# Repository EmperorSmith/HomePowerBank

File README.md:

# HomePowerBank

This project is a combined hardware-software effort around designing a control / management system for a home power bank. Unlike commercial USB power banks, this one is intended to serve as a sort of "generator substitute," having a stack of batteries large enough to supply an inverter during situations that otherwise lack power (general outage, off-grid living, etc).

# Design Goals

## Primary Goals

- Monitor a multi-cell battery stack
    - Measure cell voltage
    - Measure stack voltage
    - Measure stack current
    - Measure temperatures
    - Estimate cell state-of-charge
- Report monitored state to user
- Accept and react to user input for basic operations
- Protect pack against fault conditions
    - Overvoltage / Overcharge
    - Undervoltage / Undercharge
    - Overcurrent
    - Overtemperature
- Integrate control of external charger and inverter
    - Connect & disconnect battery stack bus and external devices
    - Produce on/off control output to charger
    - Take in fault input from charger
    - Produce on/off control output to inverter
    - Take in fault input from inverter

## Secondary Goals

- Provide bidirectional USB-C charging port
    - Supply external loads with 5V 1.5A power
    - Trickle-charge bank from external supply
- Take control commands from external communication interface
- Implement advanced diagnostics
- Implement flexible / extensible stack architecture
    - Adapt to different cell and IC counts
    - Adapt to different cell chemistries

# Tools

As much as possible, the tools used to produce the design should be freely available.

- Circuit schematic and layout creation will take place in [KiCAD](www.kicad.org)
- Block diagrams and similar drawing should use [draw.io](www.diagrams.net)
- Circuit simulations should be conducted in a free SPICE tool, like [ngspice](https://ngspice.sourceforge.io/) or [LTSpice](https://www.analog.com/en/resources/design-tools-and-calculators/ltspice-simulator.html)
- Documentation should be created using the Markdown language / format

# Philosophy

## System Design

When in doubt, design should err on the side of over-engineering, especially for the prototype phase.

## Project Code of Conduct

"Be excellent to each other" *- Bill S. Preston, Esq.*

## Usability

The system in basic form should be fully usable from the standpoint of a non-engineer, but should also offer the capabilities for a knowledgeable person to modify / alter the system to their desires.

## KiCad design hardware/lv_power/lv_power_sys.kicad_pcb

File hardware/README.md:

# System Blocks

## Internal Power Supply

### Description

This system will take the battery bank voltage and convert it to 5V to supply various aspects of the system (microcontroller, USB port, maybe even the BMS chips).

With the battery bank currently targeted at a 16S LFP configuration, this limits the maximum voltage to about 55V. Conventional buck regulators should be able to convert at this ratio and voltage range. It is also permissible to use a flyback regulator, although this will present additional challenges over a buck regulator.

If other system rails are needed, secondary voltage regulators will be added.

There will be a secondary LV battery backup system to ensure that faults with the main bank will not cause immediate shutdown of the system. This is to ensure good shutdown and startup behavior and preserve information about the system.

### Requirements

- Input Voltage : 32V to 56V
- Input Current : (as needed)
- Output Voltage : 5V +/- 0.2V
- Output Current : at least 1.5A, no more than 3A

## Trickle Charge Circuit

### Description

This system will take in 5V from the USB port and boost it up to about 55V to trickle-charge the battery bank.

The power conversion topology chosen is a flyback converter. The step-up ratio is just too large to use a conventional boost converter.

Ideally, the output of the buck regulator will have a constant-current-limiting circuit attached to it to accommodate a wide range of battery bank voltages.

### Requirements

- Input Voltage : 5.0V +/- 0.25V
- Input Current : no more than 1A average
- Output Voltage : 53V +/- 2V
- Output Current : no more than 50mA

## USB Interface

### Description

A USB C socket will be present on the unit. It will be capable of both supplying power to an external load and drawing power from an external source.

### Requirements

Despite having a USB C connector, the port will not have full USB 3 communication capabilities. If communication is added, it will be USB 2.x compliant only.

While the port will be able to both source and sink power, USB PD communication will not be implemented. Instead, a user-activated switch will determine the direction of the power flow. On switch toggle, the USB port will fully disconnect, then reconfigure the CC pins as necessary and monitor for connection.

When sourcing power, the interface will use CC pin resistor strapping to communicate the availability of up to 1.5A of current at 5.0V to downstream devices.

When sinking power, the interface will measure the CC pin voltage and respect the current limits communicated in that manner. The trickle charge circuit will not activate unless at least 1.5A of current is available from the upstream device.

The USB port will include a power switch and current sense amplifier to monitor operation. Fault conditions will trigger a port shutdown. Reconnection will be attempted after a timeout.

## Microcontroller

### Description

A local microcontroller will handle all operation and monitoring of the battery bank and attached systems (charger, inverter, USB-attached device). It will interface with users only in the most basic of manners (buttons / switches / LED indicators). More complex interactions will require an external device, to which the microcontroller will provide information for futher processing and display. The microcontroller will retain key state information across power cycles.

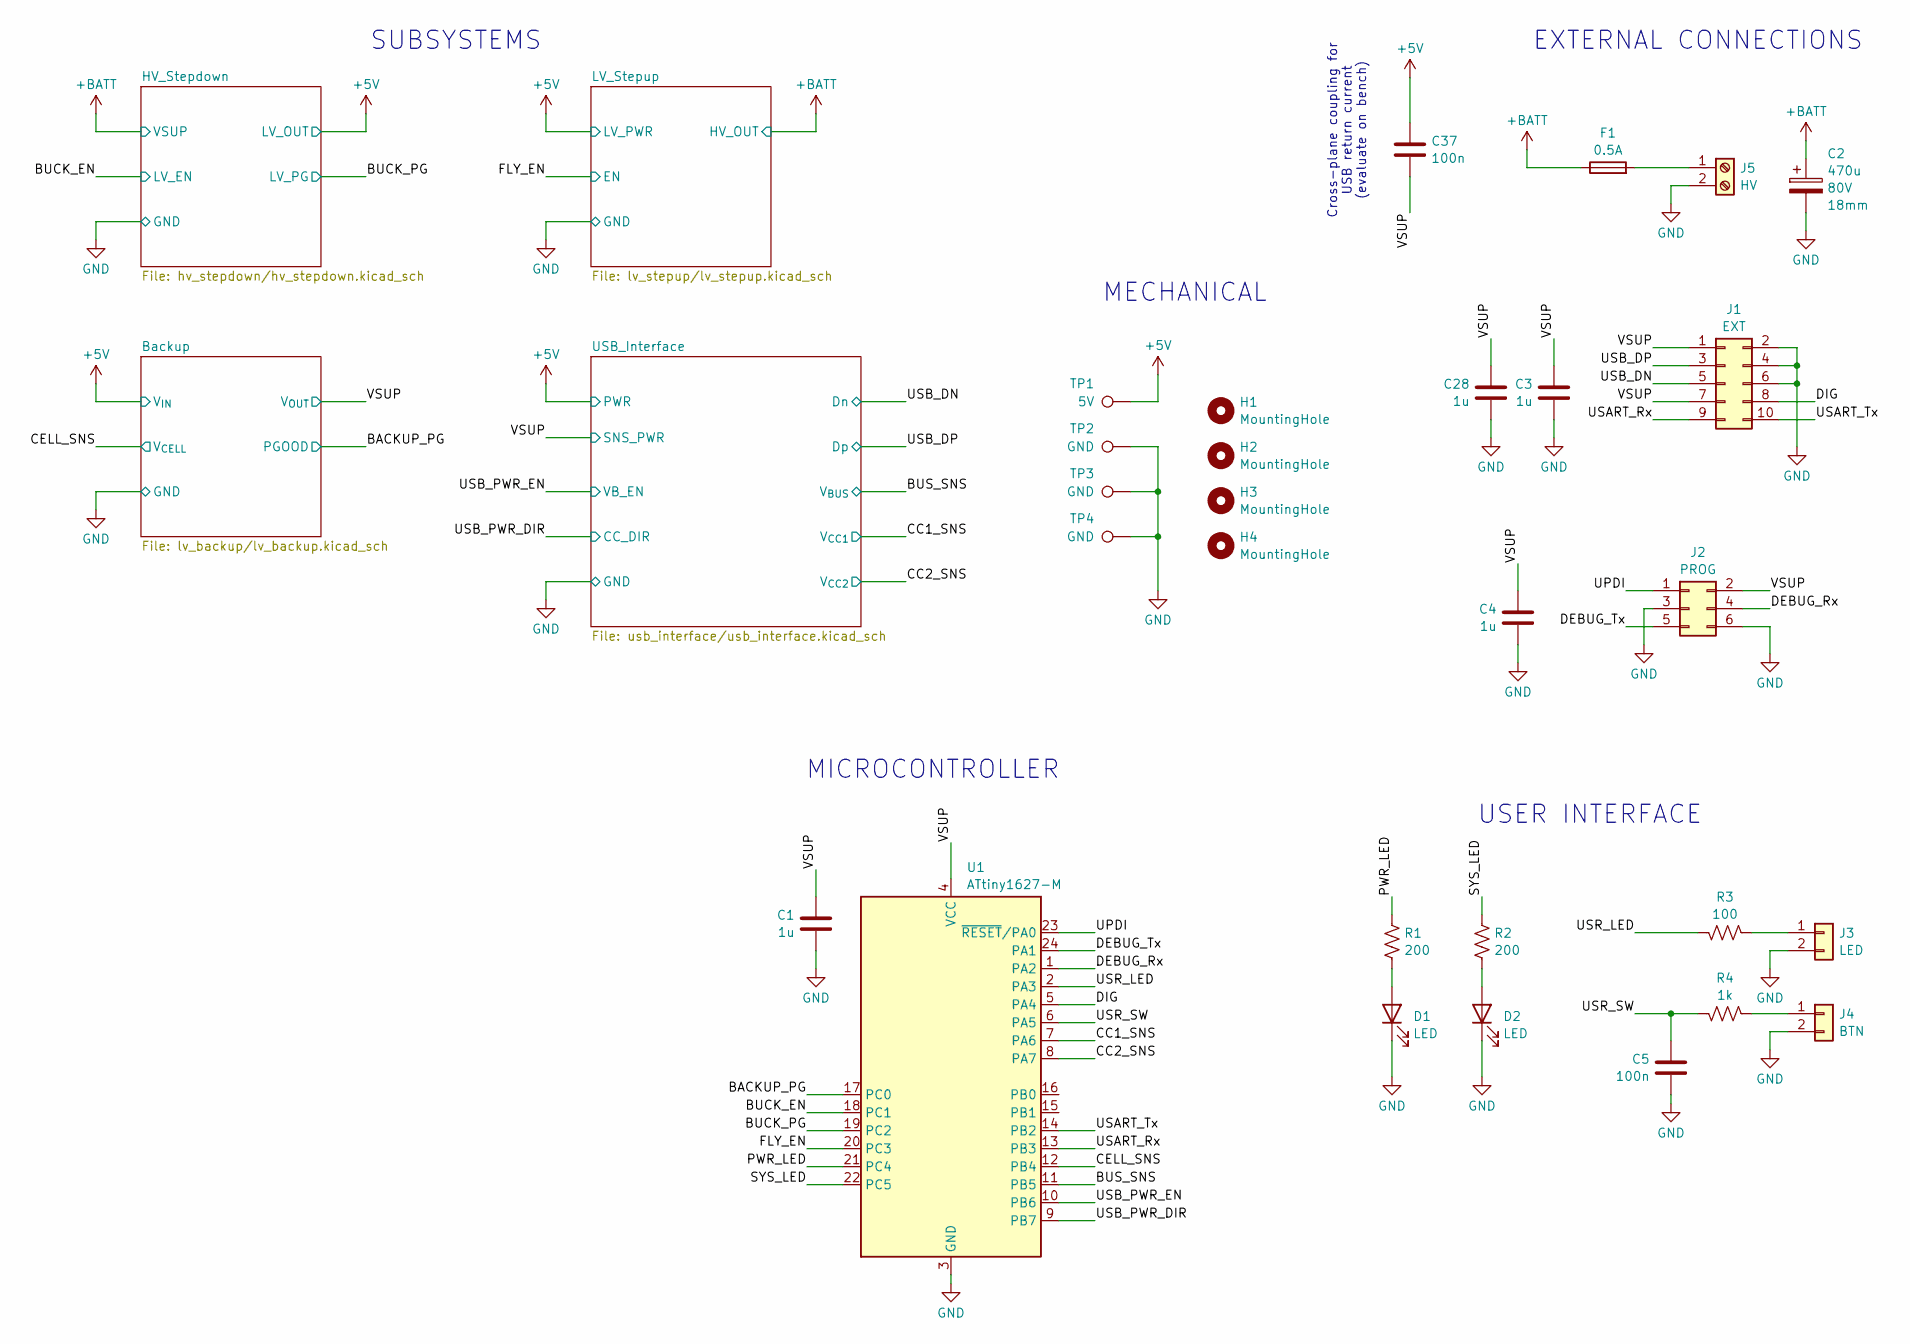
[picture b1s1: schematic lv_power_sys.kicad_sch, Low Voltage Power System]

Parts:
C1, C3, C4, C28: 1u; C_0603_1608Metric
C2: 470u; CP_Elec_18x17.5
C5, C37: 100n; C_0603_1608Metric
D1, D2: LED; D_0603_1608Metric
F1: 0.5A; Fuseholder_Clip-5x20mm_Keystone_3512_Inline_P23.62x7.27mm_D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
H1, H2, H3, H4: MountingHole; MountingHole_3.2mm_M3
J1: EXT; IDC-Header_2x05_P2.54mm_Vertical
J2: PROG; PinHeader_2x03_P2.54mm_Vertical
J3: LED; PinHeader_1x02_P2.54mm_Vertical
J4: BTN; PinHeader_1x02_P2.54mm_Vertical
J5: HV; SolderWire-0.15sqmm_1x02_P4mm_D0.5mm_OD1.5mm
R1, R2: 200; R_0603_1608Metric
R3: 100; R_0603_1608Metric
R4: 1k; R_0603_1608Metric
TP1: 5V; TestPoint_Pad_D1.5mm
TP2, TP3, TP4: GND; TestPoint_Pad_D1.5mm
U1: ATtiny1627-M; QFN-24-1EP_4x4mm_P0.5mm_EP2.6x2.6mm

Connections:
+5V: C37.1, TP1.1; also elsewhere on the board
+BATT: C2.1, F1.1; also elsewhere on the board
/BACKUP_PG: U1.17 (PC0); also elsewhere on the board
/BUCK_EN: U1.18 (PC1); also elsewhere on the board
/BUCK_PG: U1.19 (PC2); also elsewhere on the board
/BUS_SNS: U1.11 (PB5); also elsewhere on the board
/CC1_SNS: U1.7 (PA6); also elsewhere on the board
/CC2_SNS: U1.8 (PA7); also elsewhere on the board
/CELL_SNS: U1.12 (PB4); also elsewhere on the board
/DEBUG_Rx: J2.4, U1.1 (PA2)
/DEBUG_Tx: J2.5, U1.24 (PA1)
/DIG: J1.8, U1.5 (PA4)
/FLY_EN: U1.20 (PC3); also elsewhere on the board
/LED0: R1.2, U1.21 (PC4)
/LED1: R2.2, U1.22 (PC5)
/UPDI: J2.1, U1.23 (~RESET/PA0)
/USART_Rx: J1.9, U1.13 (PB3)
/USART_Tx: J1.10, U1.14 (PB2)
/USB_DN: J1.5; also elsewhere on the board
/USB_DP: J1.3; also elsewhere on the board
/USB_PWR_DIR: U1.9 (PB7); also elsewhere on the board
/USB_PWR_EN: U1.10 (PB6); also elsewhere on the board
/USR_LED: R3.1, U1.2 (PA3)
/USR_SW: C5.1, R4.1, U1.6 (PA5)
/VSUP: C1.1, C3.1, C4.1, C28.1, C37.2, J1.1, J1.7, J2.2, U1.4 (VCC); also elsewhere on the board
GND: C1.2, C2.2, C3.2, C4.2, C5.2, C28.2, D1.1 (K), D2.1 (K), J1.2, J1.4, J1.6, J2.3, J2.6, J3.2, J4.2, J5.2, TP2.1, TP3.1, TP4.1, U1.3 (GND), U1.25 (GND); also elsewhere on the board
unnamed: D1.2 (A), R1.1
unnamed: D2.2 (A), R2.1
unnamed: J3.1, R3.2
unnamed: J4.1, R4.2
unnamed: F1.2, J5.1

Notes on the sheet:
USER INTERFACE
SUBSYSTEMS
EXTERNAL CONNECTIONS
Cross-plane coupling for USB return current (evaluate on bench)
MECHANICAL
MICROCONTROLLER

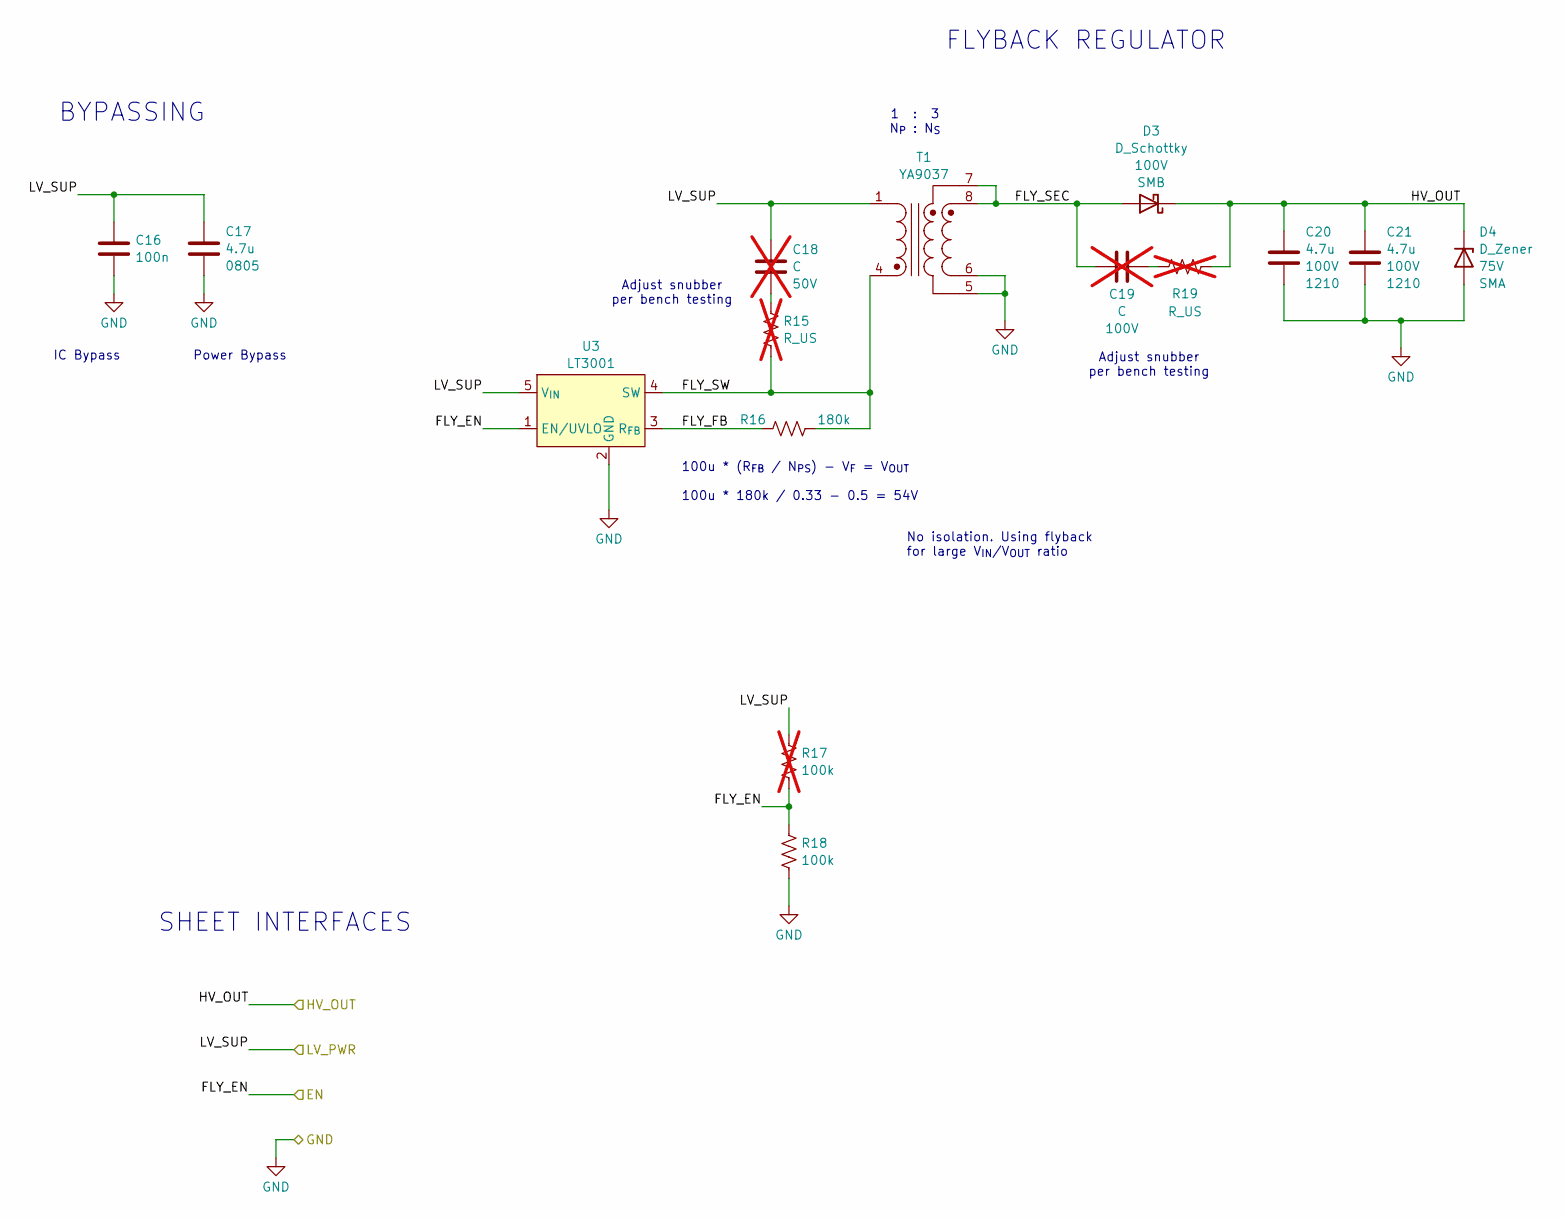
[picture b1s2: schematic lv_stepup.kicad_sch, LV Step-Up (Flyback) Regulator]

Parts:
C16: 100n; C_0603_1608Metric
C17: 4.7u; C_0805_2012Metric
C18, C19: C; C_0603_1608Metric; not fitted
C20, C21: 4.7u; C_1210_3225Metric
D3: D_Schottky; D_SMB
D4: D_Zener; D_SMA
R15, R19: R_US; R_0603_1608Metric; not fitted
R16: 180k; R_0603_1608Metric
R17: 100k; R_0603_1608Metric; not fitted
R18: 100k; R_0603_1608Metric
T1: YA9037; Coilcraft_YA903x
U3: LT3001; SOT-23-5

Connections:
+5V: C16.1, C17.1, C18.1, R17.2, T1.1, U3.5 (V_{IN}); also elsewhere on the board
+BATT: C20.1, C21.1, D3.1 (K), D4.1 (K), R19.2; also elsewhere on the board
/FLY_EN: R17.1, R18.2, U3.1 (EN/UVLO); also elsewhere on the board
/LV_Stepup/FLY_FB: R16.1, U3.3 (R_{FB})
/LV_Stepup/FLY_SEC: C19.1, D3.2 (A), T1.7, T1.8
/LV_Stepup/FLY_SW: R15.1, R16.2, T1.4, U3.4 (SW)
GND: C16.2, C17.2, C20.2, C21.2, D4.2 (A), R18.1, T1.5, T1.6, U3.2 (GND); also elsewhere on the board
unnamed: C18.2, R15.2
unnamed: C19.2, R19.1

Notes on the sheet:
No isolation. Using flyback for large V_{IN}/V_{OUT} ratio
IC Bypass
1 : 3 N_{P} : N_{S}
FLYBACK REGULATOR
100u * (R_{FB} / N_{PS}) - V_{F} = V_{OUT} 100u * 180k / 0.33 - 0.5 = 54V
SHEET INTERFACES
Adjust snubber per bench testing
Power Bypass
BYPASSING

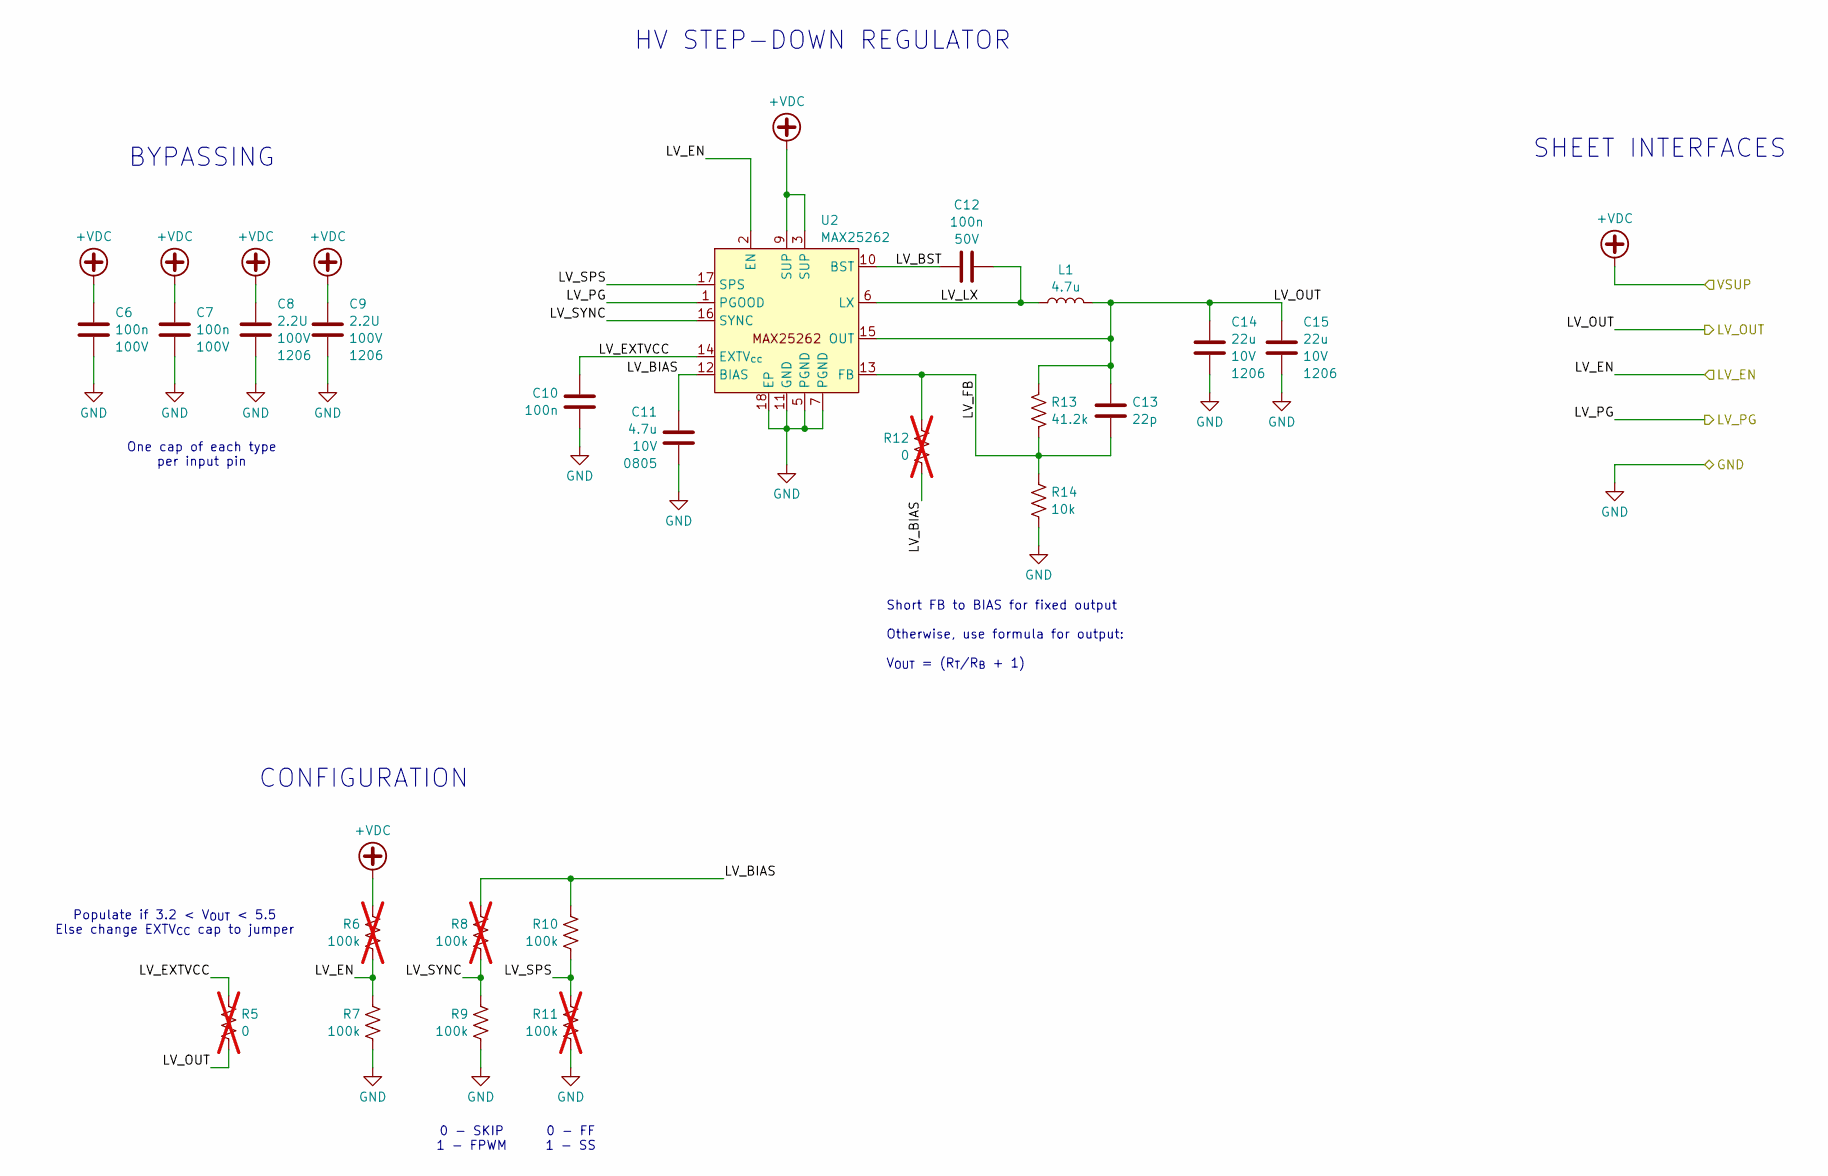
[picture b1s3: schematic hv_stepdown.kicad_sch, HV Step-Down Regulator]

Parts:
C6, C7, C10, C12: 100n; C_0603_1608Metric
C8, C9: 2.2U; C_1210_3225Metric
C11: 4.7u; C_0805_2012Metric
C13: 22p; C_0603_1608Metric
C14, C15: 22u; C_1210_3225Metric
L1: 4.7u; L_Coilcraft_XAL6060-XXX
R5, R12: 0; R_0603_1608Metric; not fitted
R6, R8, R11: 100k; R_0603_1608Metric; not fitted
R7, R9, R10: 100k; R_0603_1608Metric
R13: 41.2k; R_0603_1608Metric
R14: 10k; R_0603_1608Metric
U2: MAX25262; ADI_21-100429

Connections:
+5V: C13.2, C14.2, C15.2, L1.2, R5.1, R13.2, U2.15 (OUT); also elsewhere on the board
+BATT: C6.1, C7.1, C8.1, C9.1, R6.1, U2.3 (SUP), U2.9 (SUP); also elsewhere on the board
/BUCK_EN: R6.2, R7.1, U2.2 (EN); also elsewhere on the board
/BUCK_PG: U2.1 (PGOOD); also elsewhere on the board
/HV_Stepdown/LV_BIAS: C11.2, R8.1, R10.1, R12.2, U2.12 (BIAS)
/HV_Stepdown/LV_BST: C12.1, U2.10 (BST)
/HV_Stepdown/LV_EXTVCC: C10.1, R5.2, U2.14 (EXTV_{cc})
/HV_Stepdown/LV_FB: C13.1, R12.1, R13.1, R14.2, U2.13 (FB)
/HV_Stepdown/LV_LX: C12.2, L1.1, U2.6 (LX)
/HV_Stepdown/LV_SPS: R10.2, R11.1, U2.17 (SPS)
/HV_Stepdown/LV_SYNC: R8.2, R9.1, U2.16 (SYNC)
GND: C6.2, C7.2, C8.2, C9.2, C10.2, C11.1, C14.1, C15.1, R7.2, R9.2, R11.2, R14.1, U2.5 (PGND), U2.7 (PGND), U2.11 (GND), U2.18 (EP); also elsewhere on the board

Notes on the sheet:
HV STEP-DOWN REGULATOR
0 - SKIP 1 - FPWM
Populate if 3.2 < V_{OUT} < 5.5 Else change EXTV_{CC} cap to jumper
0 - FF 1 - SS
SHEET INTERFACES
Short FB to BIAS for fixed output Otherwise, use formula for output: V_{OUT} = (R_{T}/R_{B} + 1)
CONFIGURATION
BYPASSING
One cap of each type per input pin

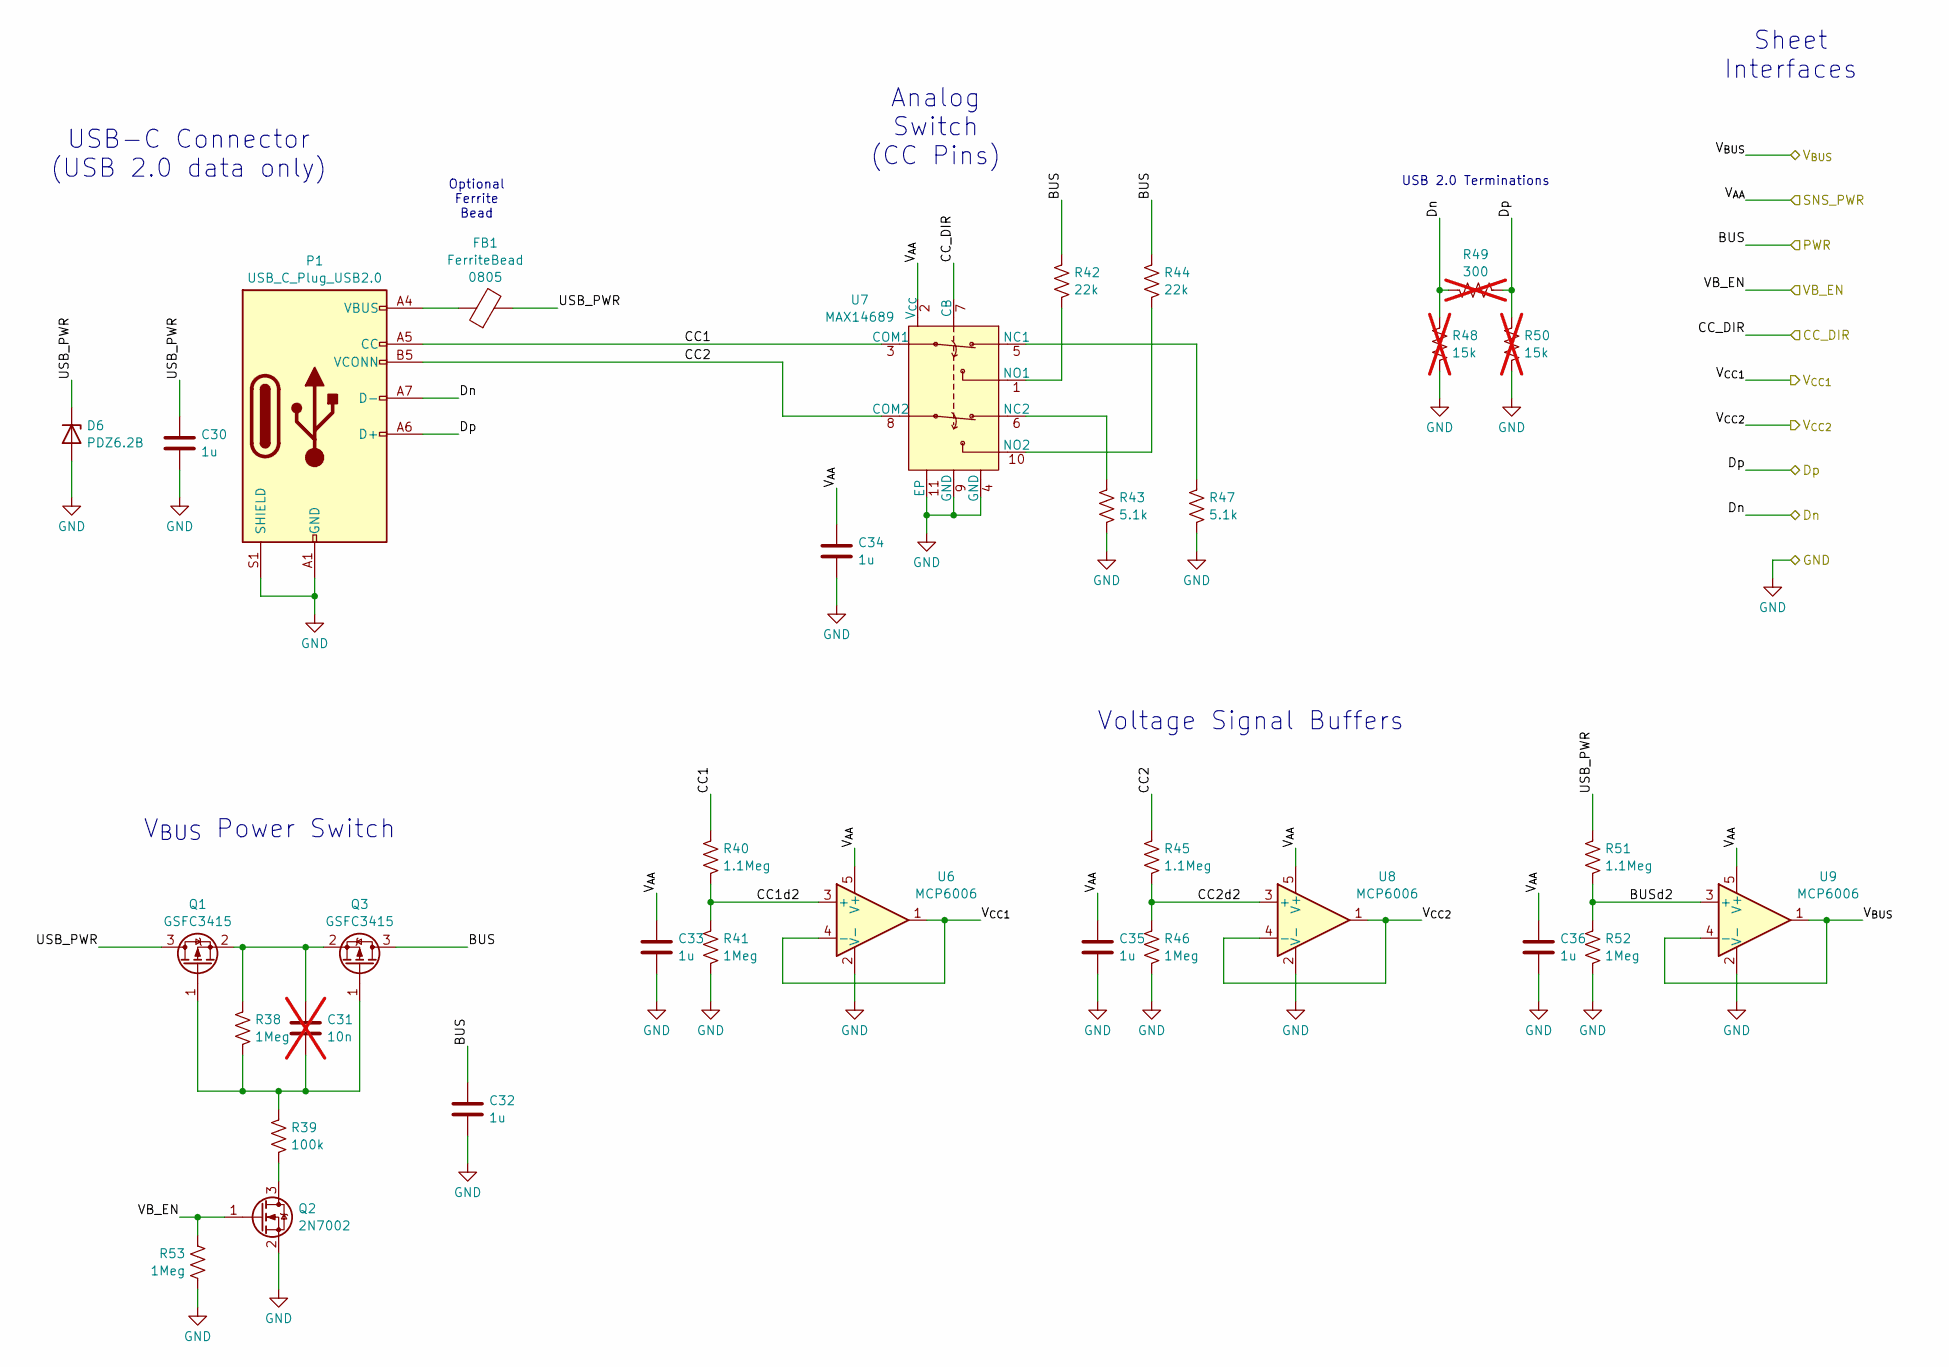
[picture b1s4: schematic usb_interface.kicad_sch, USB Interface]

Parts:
C30, C32, C33, C34, C35, C36: 1u; C_0603_1608Metric_Pad1.08x0.95mm_HandSolder
C31: 10n; C_0603_1608Metric; not fitted
D6: PDZ6.2B; D_SOD-123
FB1: FerriteBead; L_0805_2012Metric
P1: USB_C_Plug_USB2.0; USB_C_Receptacle_GCT_USB4085
Q1, Q3: GSFC3415; SOT-23
Q2: 2N7002; SOT-23
R38, R41, R46, R52, R53: 1Meg; R_0603_1608Metric
R39: 100k; R_0603_1608Metric
R40, R45, R51: 1.1Meg; R_0603_1608Metric
R42, R44: 22k; R_0603_1608Metric
R43, R47: 5.1k; R_0603_1608Metric
R48, R50: 15k; R_0603_1608Metric; not fitted
R49: 300; R_0603_1608Metric; not fitted
U6, U8, U9: MCP6006; TSOT-23-5
U7: MAX14689; ADI_21-100013A

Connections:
+5V: C32.1, Q3.3 (D), R42.1, R44.1; also elsewhere on the board
/BUS_SNS: U9.1, U9.4 (-); also elsewhere on the board
/CC1_SNS: U6.1, U6.4 (-); also elsewhere on the board
/CC2_SNS: U8.1, U8.4 (-); also elsewhere on the board
/USB_DN: P1.A7 (D-), R48.1, R49.1; also elsewhere on the board
/USB_DP: P1.A6 (D+), R49.2, R50.1; also elsewhere on the board
/USB_Interface/BUSd2: R51.2, R52.1, U9.3 (+)
/USB_Interface/CC1: P1.A5 (CC), R40.1, U7.3 (COM1)
/USB_Interface/CC1d2: R40.2, R41.1, U6.3 (+)
/USB_Interface/CC2: P1.B5 (VCONN), R45.1, U7.8 (COM2)
/USB_Interface/CC2d2: R45.2, R46.1, U8.3 (+)
/USB_Interface/USB_PWR: C30.1, D6.1 (K), FB1.2, Q1.3 (D), R51.1
/USB_PWR_DIR: U7.7 (CB); also elsewhere on the board
/USB_PWR_EN: Q2.1 (G), R53.1; also elsewhere on the board
/VSUP: C33.1, C34.1, C35.1, C36.1, U6.5 (V+), U7.2 (V_{CC}), U8.5 (V+), U9.5 (V+); also elsewhere on the board
GND: C30.2, C32.2, C33.2, C34.2, C35.2, C36.2, D6.2 (A), P1.A1 (GND), P1.A12 (GND), P1.B1 (GND), P1.B12 (GND), P1.S1 (SHIELD), Q2.2 (S), R41.2, R43.2, R46.2, R47.2, R48.2, R50.2, R52.2, R53.2, U6.2 (V-), U7.4 (GND), U7.9 (GND), U7.11 (EP), U8.2 (V-), U9.2 (V-); also elsewhere on the board
unnamed: FB1.1, P1.A4 (VBUS), P1.A9 (VBUS), P1.B4 (VBUS), P1.B9 (VBUS)
unnamed: C31.2, Q1.1 (G), Q3.1 (G), R38.2, R39.1
unnamed: C31.1, Q1.2 (S), Q3.2 (S), R38.1
unnamed: Q2.3 (D), R39.2
unnamed: R47.1, U7.5 (NC1)
unnamed: R43.1, U7.6 (NC2)
unnamed: R42.2, U7.1 (NO1)
unnamed: R44.2, U7.10 (NO2)

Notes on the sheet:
Sheet Interfaces
V_{BUS} Power Switch
Analog Switch (CC Pins)
Optional Ferrite Bead
Voltage Signal Buffers
USB-C Connector (USB 2.0 data only)
USB 2.0 Terminations

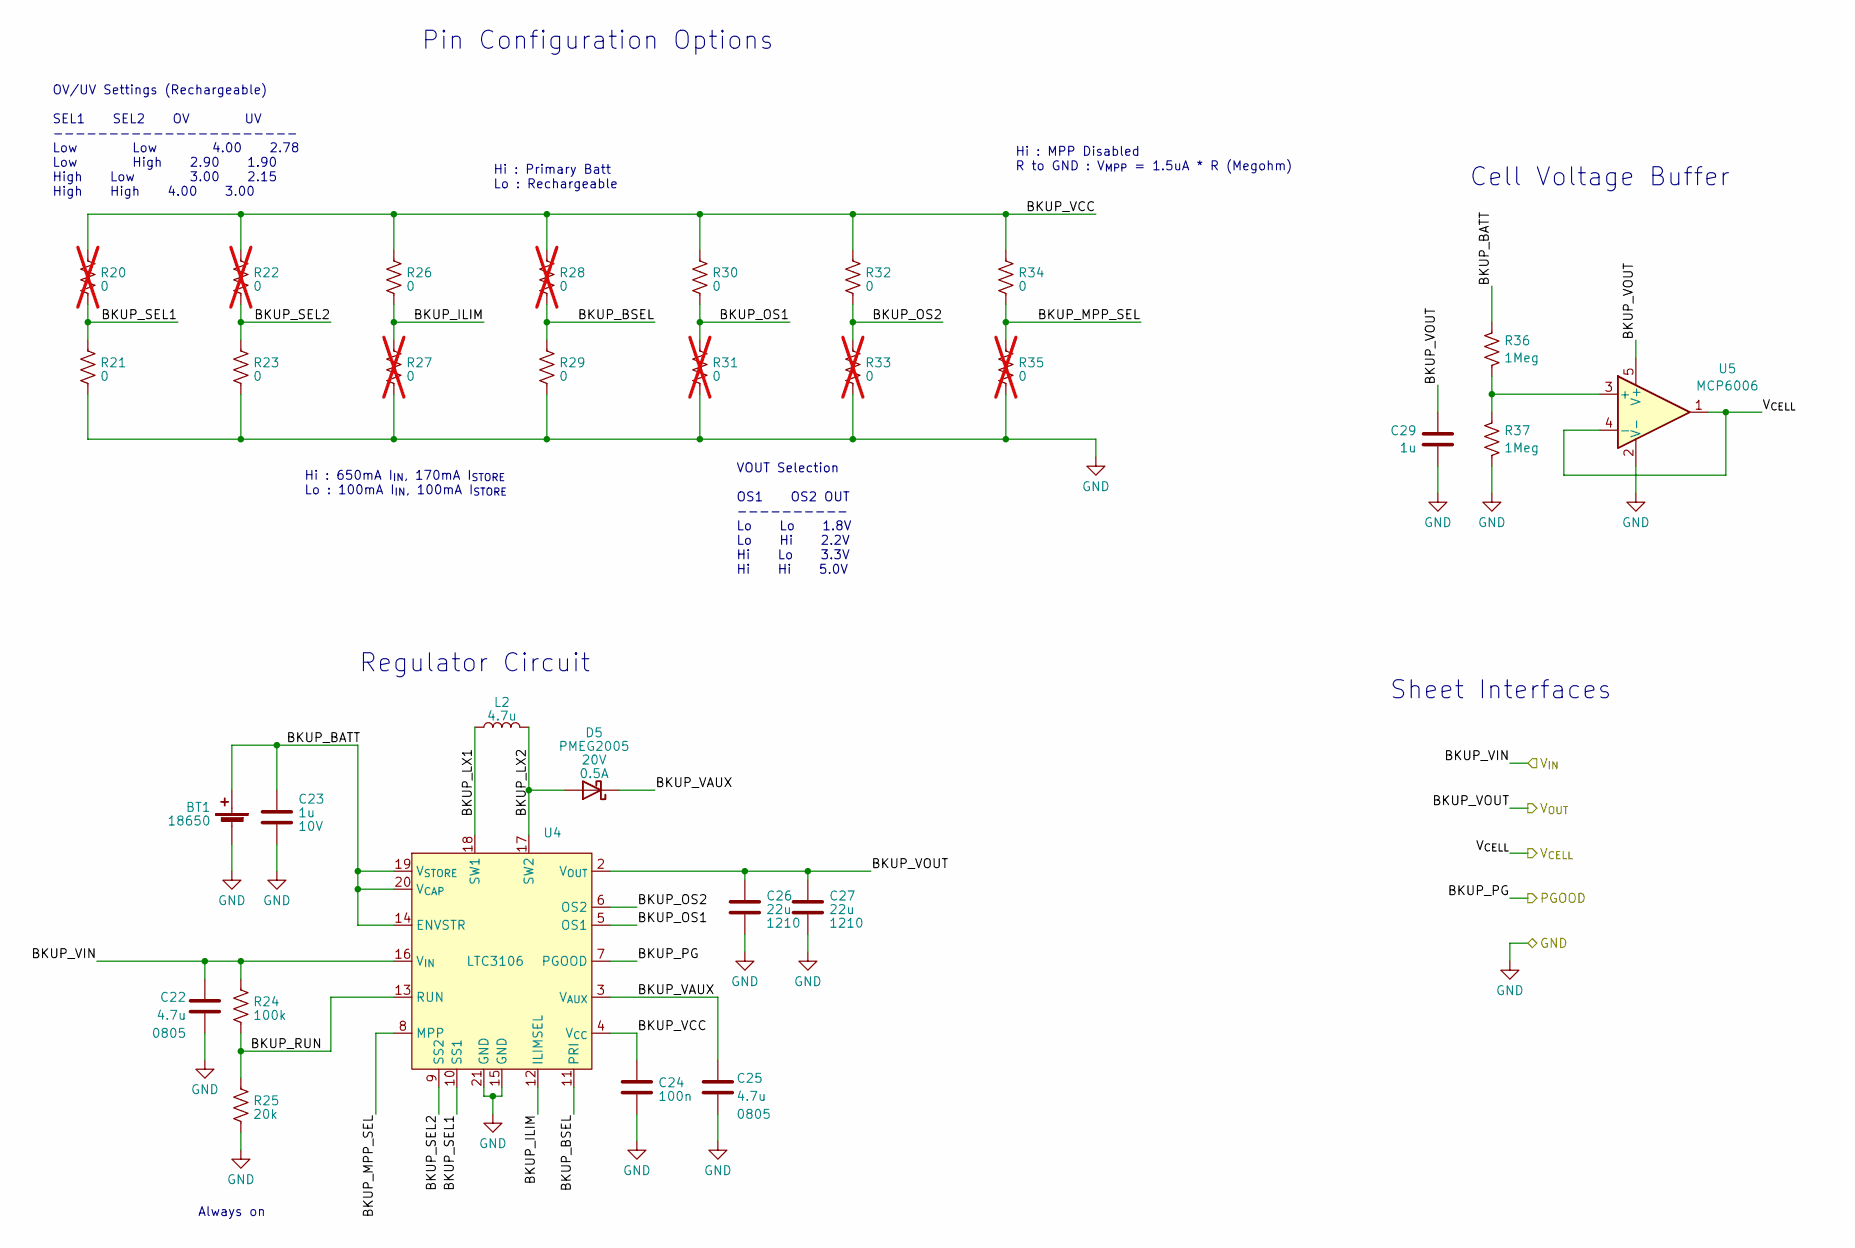
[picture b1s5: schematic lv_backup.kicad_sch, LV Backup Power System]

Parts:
BT1: 18650; BatteryHolder_Keystone_1042_1x18650
C22, C25: 4.7u; C_0805_2012Metric
C23: 1u; C_0603_1608Metric_Pad1.08x0.95mm_HandSolder
C24: 100n; C_0603_1608Metric
C26, C27: 22u; C_1210_3225Metric
C29: 1u; C_0603_1608Metric
D5: PMEG2005; D_SOD-123F
L2: 4.7u; L_Coilcraft_XAL4040-XXX
R20, R22, R27, R28, R31, R33, R35: 0; R_0603_1608Metric; not fitted
R21, R23, R26, R29, R30, R32, R34: 0; R_0603_1608Metric
R24: 100k; R_0603_1608Metric
R25: 20k; R_0603_1608Metric
R36, R37: 1Meg; R_0603_1608Metric
U4: LTC3106; QFN-20-1EP_3x4mm_P0.5mm_EP1.65x2.65mm
U5: MCP6006; TSOT-23-5

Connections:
+5V: C22.1, R24.1, U4.16 (V_{IN}); also elsewhere on the board
/BACKUP_PG: U4.7 (PGOOD); also elsewhere on the board
/Backup/BKUP_BATT: BT1.1 (+), C23.1, R36.1, U4.14 (ENVSTR), U4.19 (V_{STORE}), U4.20 (V_{CAP})
/Backup/BKUP_BSEL: R28.2, R29.1, U4.11 (PRI)
/Backup/BKUP_ILIM: R26.2, R27.1, U4.12 (ILIMSEL)
/Backup/BKUP_LX1: L2.1, U4.18 (SW1)
/Backup/BKUP_LX2: D5.2 (A), L2.2, U4.17 (SW2)
/Backup/BKUP_MPP_SEL: R34.2, R35.1, U4.8 (MPP)
/Backup/BKUP_OS1: R30.2, R31.1, U4.5 (OS1)
/Backup/BKUP_OS2: R32.2, R33.1, U4.6 (OS2)
/Backup/BKUP_RUN: R24.2, R25.1, U4.13 (RUN)
/Backup/BKUP_SEL1: R20.2, R21.1, U4.10 (SS1)
/Backup/BKUP_SEL2: R22.2, R23.1, U4.9 (SS2)
/Backup/BKUP_VAUX: C25.1, D5.1 (K), U4.3 (V_{AUX})
/Backup/BKUP_VCC: C24.1, R20.1, R22.1, R26.1, R28.1, R30.1, R32.1, R34.1, U4.4 (V_{CC})
/CELL_SNS: U5.1, U5.4 (-); also elsewhere on the board
/VSUP: C26.1, C27.1, C29.1, U4.2 (V_{OUT}), U5.5 (V+); also elsewhere on the board
GND: BT1.2 (-), C22.2, C23.2, C24.2, C25.2, C26.2, C27.2, C29.2, R21.2, R23.2, R25.2, R27.2, R29.2, R31.2, R33.2, R35.2, R37.2, U4.15 (GND), U4.21 (GND), U5.2 (V-); also elsewhere on the board
unnamed: R36.2, R37.1, U5.3 (+)

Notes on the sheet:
VOUT Selection OS1 OS2 OUT ---------- Lo Lo 1.8V Lo Hi 2.2V Hi Lo 3.3V Hi Hi 5.0V
Hi : 650mA I_{IN}, 170mA I_{STORE} Lo : 100mA I_{IN}, 100mA I_{STORE}
Sheet Interfaces
Regulator Circuit
Pin Configuration Options
Cell Voltage Buffer
Hi : MPP Disabled R to GND : V_{MPP} = 1.5uA * R (Megohm)
Always on
OV/UV Settings (Rechargeable) SEL1 SEL2 OV UV ---------------------- Low Low 4.00 2.78 Low High 2.90 1.90 High Low 3.00 2.15 High High 4.00 3.00
Hi : Primary Batt Lo : Rechargeable

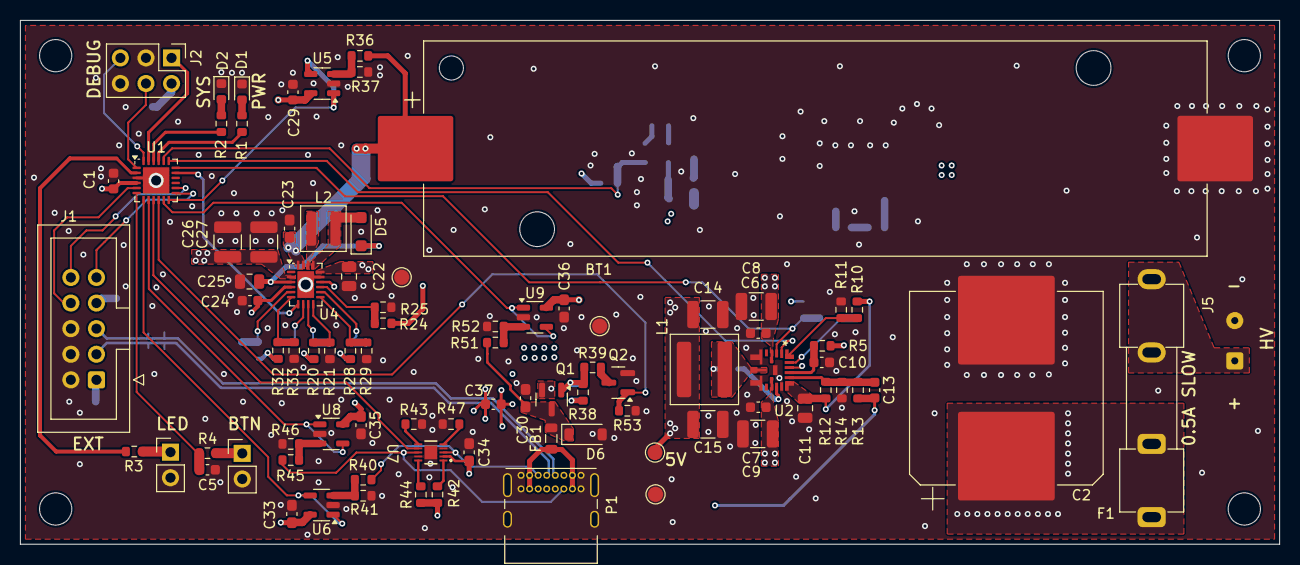
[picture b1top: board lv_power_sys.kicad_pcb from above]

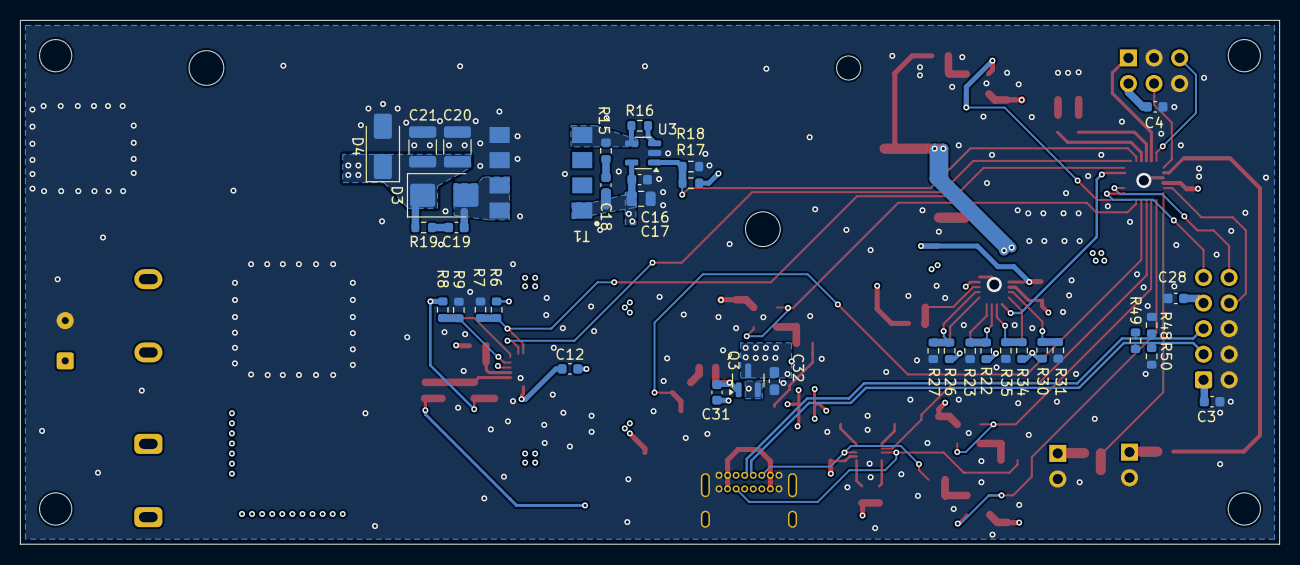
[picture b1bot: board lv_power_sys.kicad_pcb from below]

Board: 4 copper layers, 125.0 x 52.0 mm, 128 parts (37 on the bottom side), 71 nets.

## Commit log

2025-01-06 Create README.md
    initial top-level description
2025-01-06 Update README.md
    added basic design goals, started tools and philosophy sections
2025-01-10 Update README.md
    added links to KiCAD and draw.io
2025-01-10 Update LICENSE.md
    added "02paiks" to license file
2025-01-10 Create testing.txt
    added test file
2025-01-10 Create MANUAL.md
    folders, plus user manual file (no contents yet)
2025-01-10 readme files in folders
    readme files added to force folder structure
2025-01-10 expanded HW readme
    added basic description and specs for internal power and trickle charge circuits
2025-01-10 expanded sys description
    expanded system HW description, added HW block diagram
2025-01-11 added custom KiCAD symbols
    added some IC symbols to a KiCAD library for use in circuit design
2025-02-07 started uC program, created hw USB interface, created LV power backup
    started uC program (RP2040 using VSCode), added USB C port and toggles for CCx pin terminations and voltage signals/buffers, added LV power backup system (intended for microcontroller)
2025-02-07 lv backup hw update, usb interface hw update, MCU pinout spreadsheet
    added spreadsheet for mapping / allocating MCU pins and resources
    updated LV backup schematic with divider / buffer amplifier for MCU measurement
    updated USB interface voltage buffers: all have high-impedance /2 buffers
2025-02-07 hw amplifier change in lv backup and usb interface
    replaced AD8541 operational amplifier with MCP6006 (massive cost savings, on order of $1 per chip or more)
2025-02-10 expanded mcu chart
    expanded spreadsheet of MCU resource assignment
2025-02-15 library updates, mcu i2c devices
    added MAX31331 RTC to library, added EEPROM and RTC sub-schematic to MCU, expanded mcu planning chart
2025-03-08 I2C device notes
    added notes on I2C device addresses (in-schematic)
2025-09-20 huge update
    massive update; finished lv power sys hardware design, started lv power sys mcu program
